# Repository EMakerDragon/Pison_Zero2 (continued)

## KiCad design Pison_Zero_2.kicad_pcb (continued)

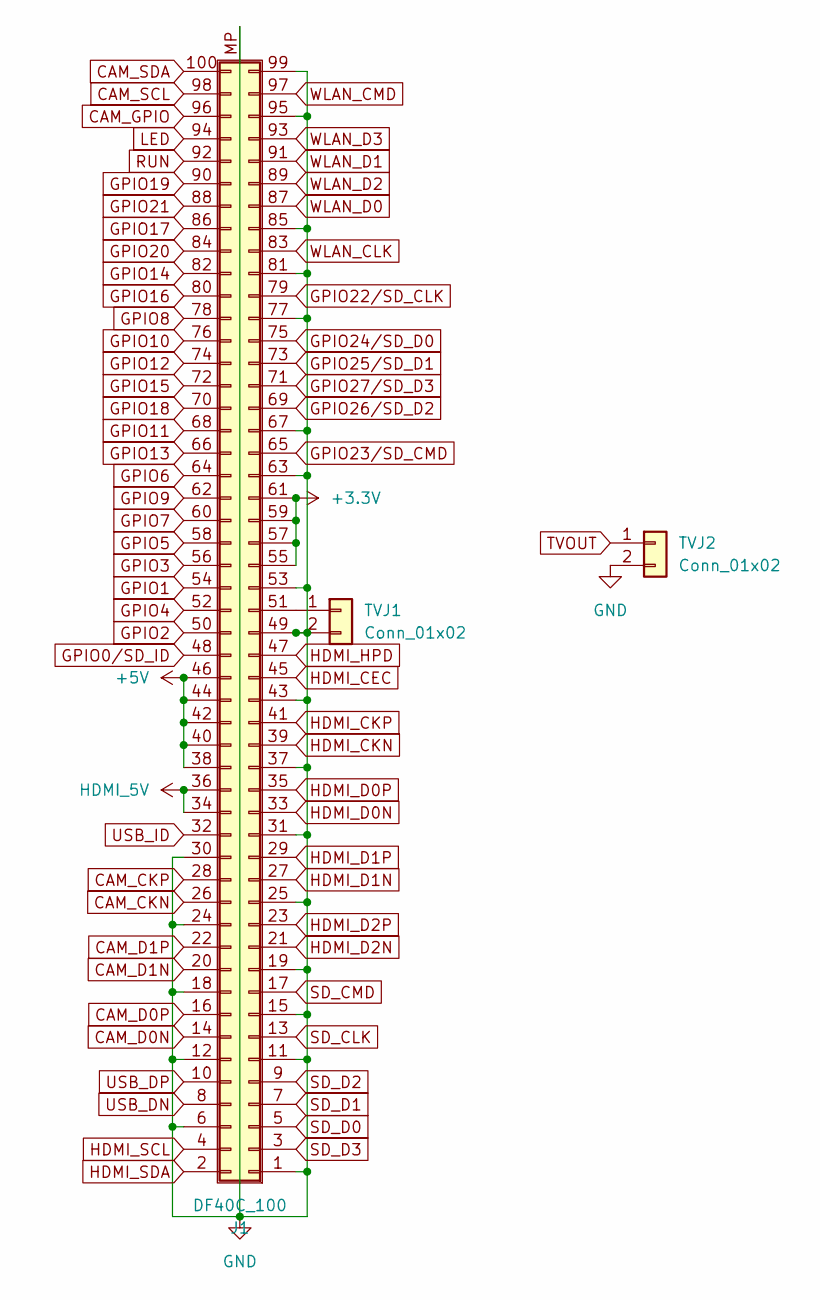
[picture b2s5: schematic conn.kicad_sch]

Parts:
J1: DF40C_100; Hirose_DF40C-100DP-0.4V_2x50-1MP_P0.4mm
TVJ1, TVJ2: Conn_01x02; SHJUMP

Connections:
+3.3V: J1.55 (Pin_a28), J1.57 (Pin_a29), J1.59 (Pin_a30), J1.61 (Pin_a31); also elsewhere on the board
+5V: J1.38 (Pin_b19), J1.40 (Pin_b20), J1.42 (Pin_b21), J1.44 (Pin_b22), J1.46 (Pin_b23); also elsewhere on the board
CAM_CKN: J1.26 (Pin_b13); also elsewhere on the board
CAM_CKP: J1.28 (Pin_b14); also elsewhere on the board
CAM_D0N: J1.14 (Pin_b7); also elsewhere on the board
CAM_D0P: J1.16 (Pin_b8); also elsewhere on the board
CAM_D1N: J1.20 (Pin_b10); also elsewhere on the board
CAM_D1P: J1.22 (Pin_b11); also elsewhere on the board
CAM_GPIO: J1.96 (Pin_b48); also elsewhere on the board
CAM_SCL: J1.98 (Pin_b49); also elsewhere on the board
CAM_SDA: J1.100 (Pin_b50); also elsewhere on the board
GND: J1.1 (Pin_a1), J1.6 (Pin_b3), J1.11 (Pin_a6), J1.12 (Pin_b6), J1.15 (Pin_a8), J1.18 (Pin_b9), J1.19 (Pin_a10), J1.24 (Pin_b12), J1.25 (Pin_a13), J1.30 (Pin_b15), J1.31 (Pin_a16), J1.37 (Pin_a19), J1.43 (Pin_a22), J1.49 (Pin_a25), J1.53 (Pin_a27), J1.63 (Pin_a32), J1.67 (Pin_a34), J1.77 (Pin_a39), J1.81 (Pin_a41), J1.85 (Pin_a43), J1.95 (Pin_a48), J1.99 (Pin_a50), J1.MP (Shield), TVJ1.2, TVJ2.2; also elsewhere on the board
GPIO0/SD_ID: J1.48 (Pin_b24); also elsewhere on the board
GPIO1: J1.54 (Pin_b27); also elsewhere on the board
GPIO2: J1.50 (Pin_b25); also elsewhere on the board
GPIO3: J1.56 (Pin_b28); also elsewhere on the board
GPIO4: J1.52 (Pin_b26); also elsewhere on the board
GPIO5: J1.58 (Pin_b29); also elsewhere on the board
GPIO6: J1.64 (Pin_b32); also elsewhere on the board
GPIO7: J1.60 (Pin_b30); also elsewhere on the board
GPIO8: J1.78 (Pin_b39); also elsewhere on the board
GPIO9: J1.62 (Pin_b31); also elsewhere on the board
GPIO10: J1.76 (Pin_b38); also elsewhere on the board
GPIO11: J1.68 (Pin_b34); also elsewhere on the board
GPIO12: J1.74 (Pin_b37); also elsewhere on the board
GPIO13: J1.66 (Pin_b33); also elsewhere on the board
GPIO14: J1.82 (Pin_b41); also elsewhere on the board
GPIO15: J1.72 (Pin_b36); also elsewhere on the board
GPIO16: J1.80 (Pin_b40); also elsewhere on the board
GPIO17: J1.86 (Pin_b43); also elsewhere on the board
GPIO18: J1.70 (Pin_b35); also elsewhere on the board
GPIO19: J1.90 (Pin_b45); also elsewhere on the board
GPIO20: J1.84 (Pin_b42); also elsewhere on the board
GPIO21: J1.88 (Pin_b44); also elsewhere on the board
GPIO22/SD_CLK: J1.79 (Pin_a40); also elsewhere on the board
GPIO23/SD_CMD: J1.65 (Pin_a33); also elsewhere on the board
GPIO24/SD_D0: J1.75 (Pin_a38); also elsewhere on the board
GPIO25/SD_D1: J1.73 (Pin_a37); also elsewhere on the board
GPIO26/SD_D2: J1.69 (Pin_a35); also elsewhere on the board
GPIO27/SD_D3: J1.71 (Pin_a36); also elsewhere on the board
HDMI_5V: J1.34 (Pin_b17), J1.36 (Pin_b18); also elsewhere on the board
HDMI_CEC: J1.45 (Pin_a23); also elsewhere on the board
HDMI_CKN: J1.39 (Pin_a20); also elsewhere on the board
HDMI_CKP: J1.41 (Pin_a21); also elsewhere on the board
HDMI_D0N: J1.33 (Pin_a17); also elsewhere on the board
HDMI_D0P: J1.35 (Pin_a18); also elsewhere on the board
HDMI_D1N: J1.27 (Pin_a14); also elsewhere on the board
HDMI_D1P: J1.29 (Pin_a15); also elsewhere on the board
HDMI_D2N: J1.21 (Pin_a11); also elsewhere on the board
HDMI_D2P: J1.23 (Pin_a12); also elsewhere on the board
HDMI_HPD: J1.47 (Pin_a24); also elsewhere on the board
HDMI_SCL: J1.4 (Pin_b2); also elsewhere on the board
HDMI_SDA: J1.2 (Pin_b1); also elsewhere on the board
LED: J1.94 (Pin_b47); also elsewhere on the board
unnamed: J1.51 (Pin_a26), TVJ1.1
RUN: J1.92 (Pin_b46); also elsewhere on the board
SD_CLK: J1.13 (Pin_a7); also elsewhere on the board
SD_CMD: J1.17 (Pin_a9); also elsewhere on the board
SD_D0: J1.5 (Pin_a3); also elsewhere on the board
SD_D1: J1.7 (Pin_a4); also elsewhere on the board
SD_D2: J1.9 (Pin_a5); also elsewhere on the board
SD_D3: J1.3 (Pin_a2); also elsewhere on the board
TVOUT: TVJ2.1; also elsewhere on the board
USB_DN: J1.8 (Pin_b4); also elsewhere on the board
USB_DP: J1.10 (Pin_b5); also elsewhere on the board
USB_ID: J1.32 (Pin_b16); also elsewhere on the board
WLAN_CLK: J1.83 (Pin_a42); also elsewhere on the board
WLAN_CMD: J1.97 (Pin_a49); also elsewhere on the board
WLAN_D0: J1.87 (Pin_a44); also elsewhere on the board
WLAN_D1: J1.91 (Pin_a46); also elsewhere on the board
WLAN_D2: J1.89 (Pin_a45); also elsewhere on the board
WLAN_D3: J1.93 (Pin_a47); also elsewhere on the board

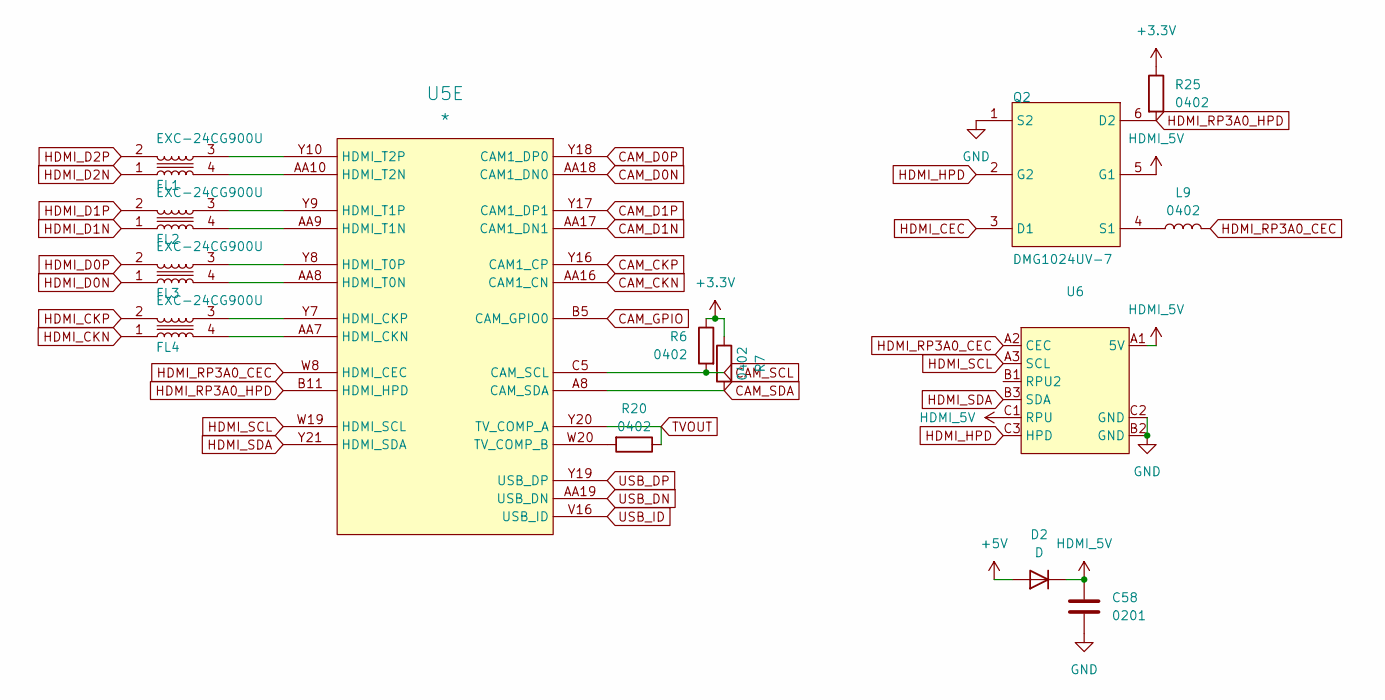
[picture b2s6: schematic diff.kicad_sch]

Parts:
C58: 0201; C_0201_0603Metric
D2: D; D_PowerDI-123
FL1, FL2, FL3, FL4: EXC-24CG900U; FIL_EXC24CB102U
L9: 0402; L_0402_1005Metric
Q2: DMG1024UV-7; SOT50P162X60-6N
R6, R7, R20, R25: 0402; R_0402_1005Metric
U5: *; RP3A0-BGA
U6: WLCSP-9_1.21x1.22mm_Layout3x3_P0.4mm

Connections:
+3.3V: R6.1, R7.1, R25.1; also elsewhere on the board
+5V: D2.2 (A); also elsewhere on the board
CAM_CKN: U5.AA16 (CAM1_CN); also elsewhere on the board
CAM_CKP: U5.Y16 (CAM1_CP); also elsewhere on the board
CAM_D0N: U5.AA18 (CAM1_DN0); also elsewhere on the board
CAM_D0P: U5.Y18 (CAM1_DP0); also elsewhere on the board
CAM_D1N: U5.AA17 (CAM1_DN1); also elsewhere on the board
CAM_D1P: U5.Y17 (CAM1_DP1); also elsewhere on the board
CAM_GPIO: U5.B5 (CAM_GPIO0); also elsewhere on the board
CAM_SCL: R6.2, U5.C5 (CAM_SCL); also elsewhere on the board
CAM_SDA: R7.2, U5.A8 (CAM_SDA); also elsewhere on the board
GND: C58.2, Q2.1 (S2), U6.B2 (GND), U6.C2 (GND); also elsewhere on the board
HDMI_5V: C58.1, D2.1 (K), Q2.5 (G1), U6.A1 (5V), U6.C1 (RPU); also elsewhere on the board
HDMI_CEC: Q2.3 (D1); also elsewhere on the board
HDMI_CKN: FL4.1; also elsewhere on the board
HDMI_CKP: FL4.2; also elsewhere on the board
HDMI_D0N: FL3.1; also elsewhere on the board
HDMI_D0P: FL3.2; also elsewhere on the board
HDMI_D1N: FL2.1; also elsewhere on the board
HDMI_D1P: FL2.2; also elsewhere on the board
HDMI_D2N: FL1.1; also elsewhere on the board
HDMI_D2P: FL1.2; also elsewhere on the board
HDMI_HPD: Q2.2 (G2), U6.C3 (HPD); also elsewhere on the board
HDMI_RP3A0_CEC: L9.2, U5.W8 (HDMI_CEC), U6.A2 (CEC)
HDMI_RP3A0_HPD: Q2.6 (D2), R25.2, U5.B11 (HDMI_HPD)
HDMI_SCL: U5.W19 (HDMI_SCL), U6.A3 (SCL); also elsewhere on the board
HDMI_SDA: U5.Y21 (HDMI_SDA), U6.B3 (SDA); also elsewhere on the board
unnamed: L9.1, Q2.4 (S1)
unnamed: FL4.4, U5.AA7 (HDMI_CKN)
unnamed: FL4.3, U5.Y7 (HDMI_CKP)
unnamed: FL3.4, U5.AA8 (HDMI_T0N)
unnamed: FL3.3, U5.Y8 (HDMI_T0P)
unnamed: FL2.4, U5.AA9 (HDMI_T1N)
unnamed: FL2.3, U5.Y9 (HDMI_T1P)
unnamed: FL1.4, U5.AA10 (HDMI_T2N)
unnamed: FL1.3, U5.Y10 (HDMI_T2P)
unnamed: R20.2, U5.W20 (TV_COMP_B)
TVOUT: R20.1, U5.Y20 (TV_COMP_A); also elsewhere on the board
USB_DN: U5.AA19 (USB_DN); also elsewhere on the board
USB_DP: U5.Y19 (USB_DP); also elsewhere on the board
USB_ID: U5.V16 (USB_ID); also elsewhere on the board

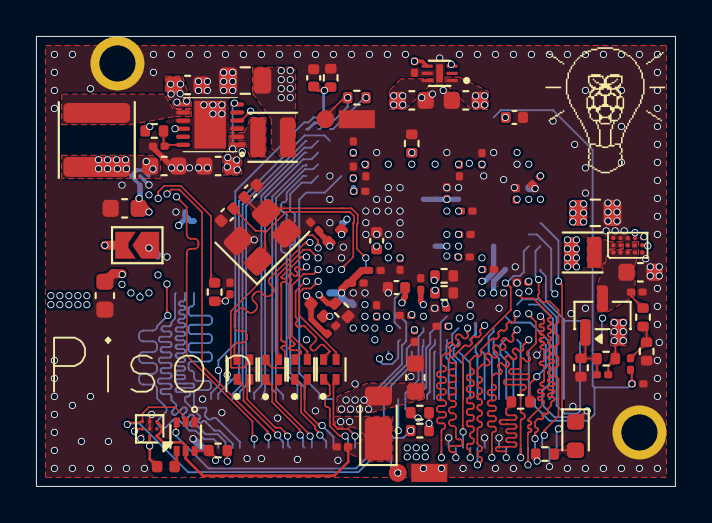
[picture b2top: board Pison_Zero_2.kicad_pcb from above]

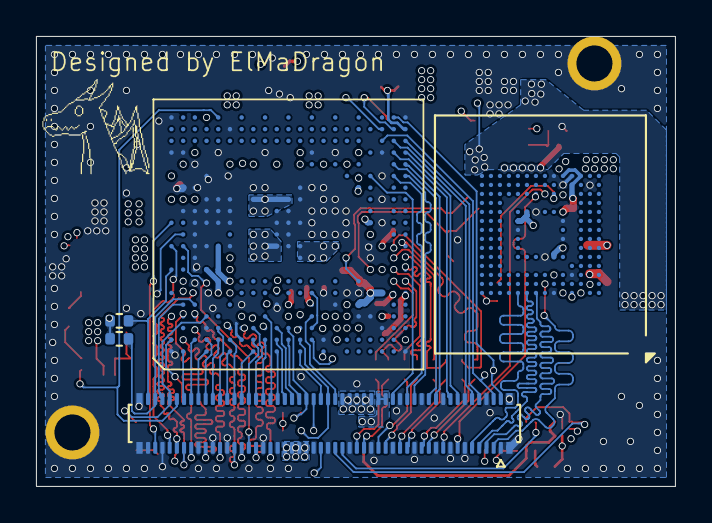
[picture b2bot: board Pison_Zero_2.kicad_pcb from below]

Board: 8 copper layers, 35.5 x 25.0 mm, 96 parts (5 on the bottom side), 121 nets.
